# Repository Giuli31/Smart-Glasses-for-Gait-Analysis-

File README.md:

# Smart Glasses for Gait Analysis in Parkinson’s Disease 
## Table of contents
* [General info](#general-info)
* [Technologies](#technologies)
* [How To Use](#how-to-use)

## General info
Parkinson’s disease (PD) is one of the most common neurodegenerative disorders of the central nervous system, which predominantly affects patients’ motor functions, movement, and stability. In recent years, there has been an increase in the usage of wearable sensors for PD symptom monitoring aiming at anticipating the disease diagnosis and thus providing a most efficient quality of care. In this context, the developed device aims to provide objective information on the motor state, analysing the patient's gait and classifying it. In order to accomplish this task, the SGGA device is based on the Timed Up and Go (TUG) test. This is a simple test to measure a person’s level of mobility. It measures the time it takes for a person to get up from a chair, walk three meters, turn around, return to the chair and sit down again. Some sources suggest that a score of 10 seconds or less indicates normal mobility; times between 11 and 20 seconds are within normal limits for elderly with fragility and disabled patients; times longer than 20 seconds indicate that the person needs external assistance and the need for further examinations and interventions. A score greater than 30 seconds suggests that the person may be prone to falls. The TUG was developed from a more articulated test, the Get-up and Go. The SGGA device isn't a classifier of Parkinson’s disease, but it can be a useful tool for the study of symptoms and progression of this disease. 

## Technologies
Project is created with:
* EAGLE - for the design of the PCB
* PSoC Creator - for the program of the microcontroller 
* PyQt5 - for the development the graphical user interface

## How To Use
* [Physical Device](#physical-device)
* [Interface](#interface)
* [Acquisition](#acquisition)
* [Bugs](#bugs)

### Physical Device
The SGGA device is a wearable device composed by two main parts. The first is a small case equipped with accelerometer and wearable on the own glasses or given glasses. The second part is a bigger case that contains the PCB and its components. It's equipped with a belt that must be fastened around the patient’s waist. On the short side of the case, it's possible to check the state of the SGGA device thanks to the presence of two LEDs. The red LED shows that the device is powered, so it works. The green LED shows the connection established between the device and the application. In particular, the green flashing LED indicates that the device is ready to send data to the application, while, when the green LED becomes fixed, it indicates that the device is sending data registered by the accelerometer to the application. 

### Interface
The graphic user interface allows the user to visualize the results of the Timed Up and Go (TUG) test. On the right side of the screen, it is possible to see a graph that shows the acceleration trend over time. On the left side there are two tabs: "Acquisition" and "Excel files". 
The tab "Acquisition" contains buttons "Start Acquisition", "Stop Acquisition", "Save Data", "New Session" and "Search for device". Here it is also possible to visualize a timer and a steps counter. 
The tab "Excel files" shows past acquisitions that are saved on Excel files named with data and progression number of session. Clicking on one of these files, it is possible to visualize on the screen a number between 0 and 2 that indicates the class of the result (0 - Normal Gait, 1 - Require further examinations, 2 - Patient need assistance). This classification is made using a machine learning model, the Decision Trees, that is trained using a set of acquisitions based on TUG test permed by healthy subject trying also to reproduce the gait of impaired people. 

### Acquisition 
The first step of the acquisition is the preparation of the patient. He/She should wear the belt and place the case on the side so that the LED lights are visible. Red LED will light up when the device is connected to the power supply. After that, the patient must wear glasses equipped with the second smaller case. Let sit the patient in the chair and so he/she is ready for the test. 

Now, the user has to run the application using the Python file named "FinalGUI.py" and start the pairing of the device with the application. Once the GUI is open, the user must push the button "Search for device" in order to connect the device, if the connection is successful the green LED will start flashing. At this point, the device is ready for start the acquisition. 

When the patient is ready to perform the test, the user has to push the button "Start Acquisition" and the timer and the steps counter start at the same time. On the graph it's possible to visualize in real-time the acceleration trend of the patient's walk. 

Once the patient has completed the test, the user has to push the button "Stop acquisition". At this point a dynamic window will open and it will show the result of the test, classifying it into "Normal gait detected", "Anomalous gait detected. Further examinations suggested" or "Serious anomalies on gait detected. Subject may require assistances". On the same window, it is asked to the user if he wants to save the result of test, in positive case clicking on "Yes". 

Now it is possible to start a new acquisition pushing again the button "Start Acquisition". 

At the end of the test, it is possible to save the entire session of acquisitions pushing the button "Save Data". These data are saved in files contained in the tab "Excel files". 

In order to start a new session of acquisitions, the user has to push the button "New session" and repeat all the previous steps. 

### Bugs
During the pairing between device and application may happen that the device fails to access the serial port. In this case, a dynamic window will open showing the wrong serial port and the message "ERROR PORT CONNECTION: ". It is recommended to reset the application.

(This project is the result of teamwork)

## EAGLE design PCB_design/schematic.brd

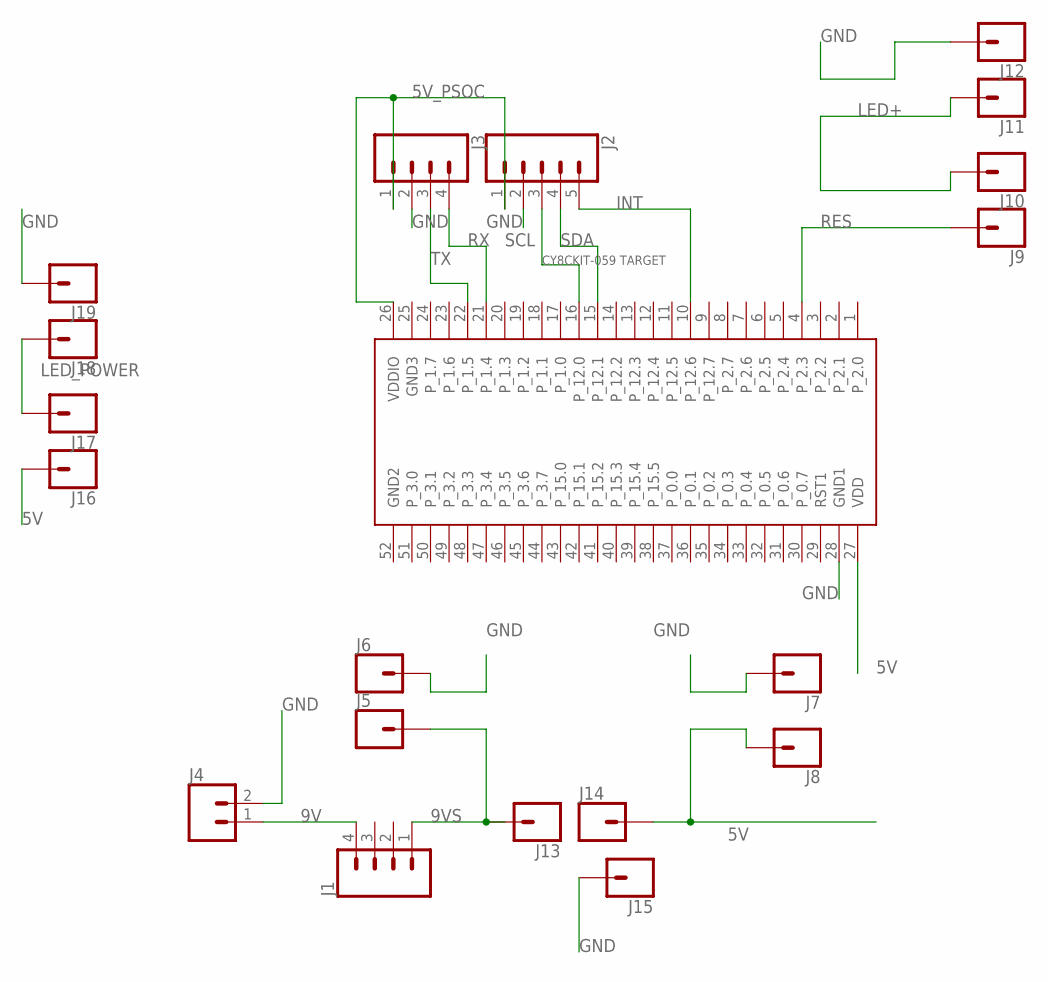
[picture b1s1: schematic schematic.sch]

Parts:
J1, J3: CONN_041X04_NO_SILK; 1X04_NO_SILK
J2: CONN_05NO_SILK; 1X05_NO_SILK
J4: CONN_021X02_NO_SILK; 1X02_NO_SILK
J5, J6, J7, J8, J9, J10, J11, J12, J13, J14, J15, J16, J17, J18, J19: CONN_01PTH_NO_SILK_YES_STOP; 1X01_NO_SILK
U$2: CY8CKIT-059_TARGET_3

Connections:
5V: J8.1, J14.1, J16.1, U$2.27 (VDD)
5V_PSOC: J2.1, J3.1, U$2.26 (VDDIO)
9V: J1.4, J4.1
9VS: J1.1, J5.1, J13.1
GND: J2.2, J3.2, J4.2, J6.1, J7.1, J12.1, J15.1, J19.1, U$2.28 (GND1)
GND2: U$2.52 (GND2)
GND3: U$2.25 (GND3)
INT: J2.5, U$2.10 (P_12.6)
LED+: J10.1, J11.1
LED_POWER: J17.1, J18.1
RES: J9.1, U$2.4 (P_2.3)
RX: J3.4, U$2.21 (P_1.4)
SCL: J2.3, U$2.16 (P_12.0)
SDA: J2.4, U$2.15 (P_12.1)
TX: J3.3, U$2.22 (P_1.5)

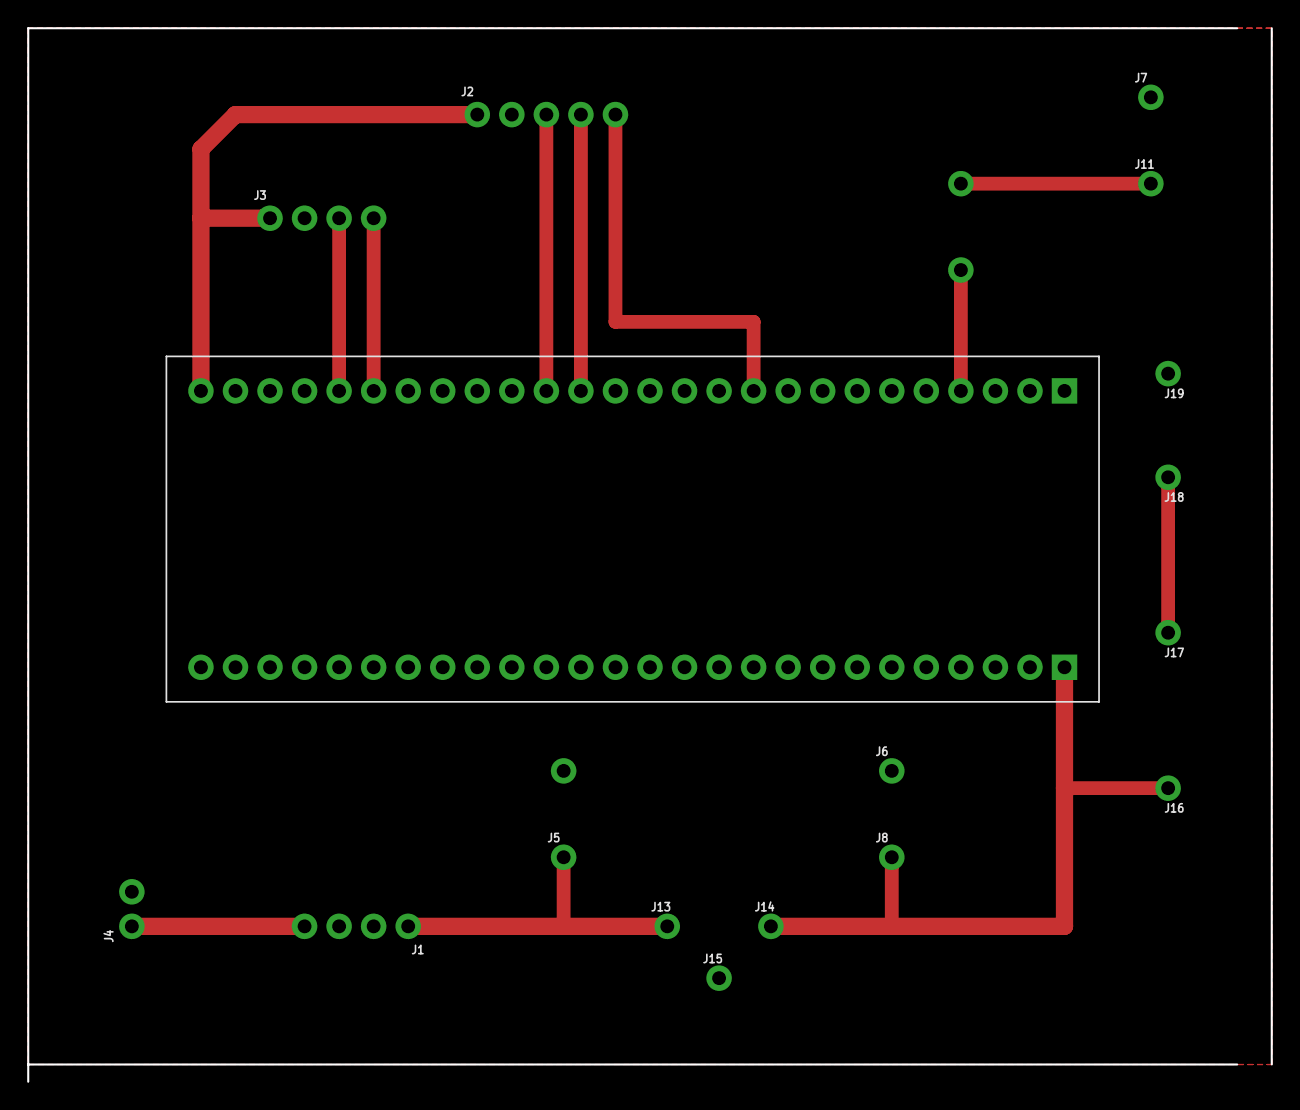
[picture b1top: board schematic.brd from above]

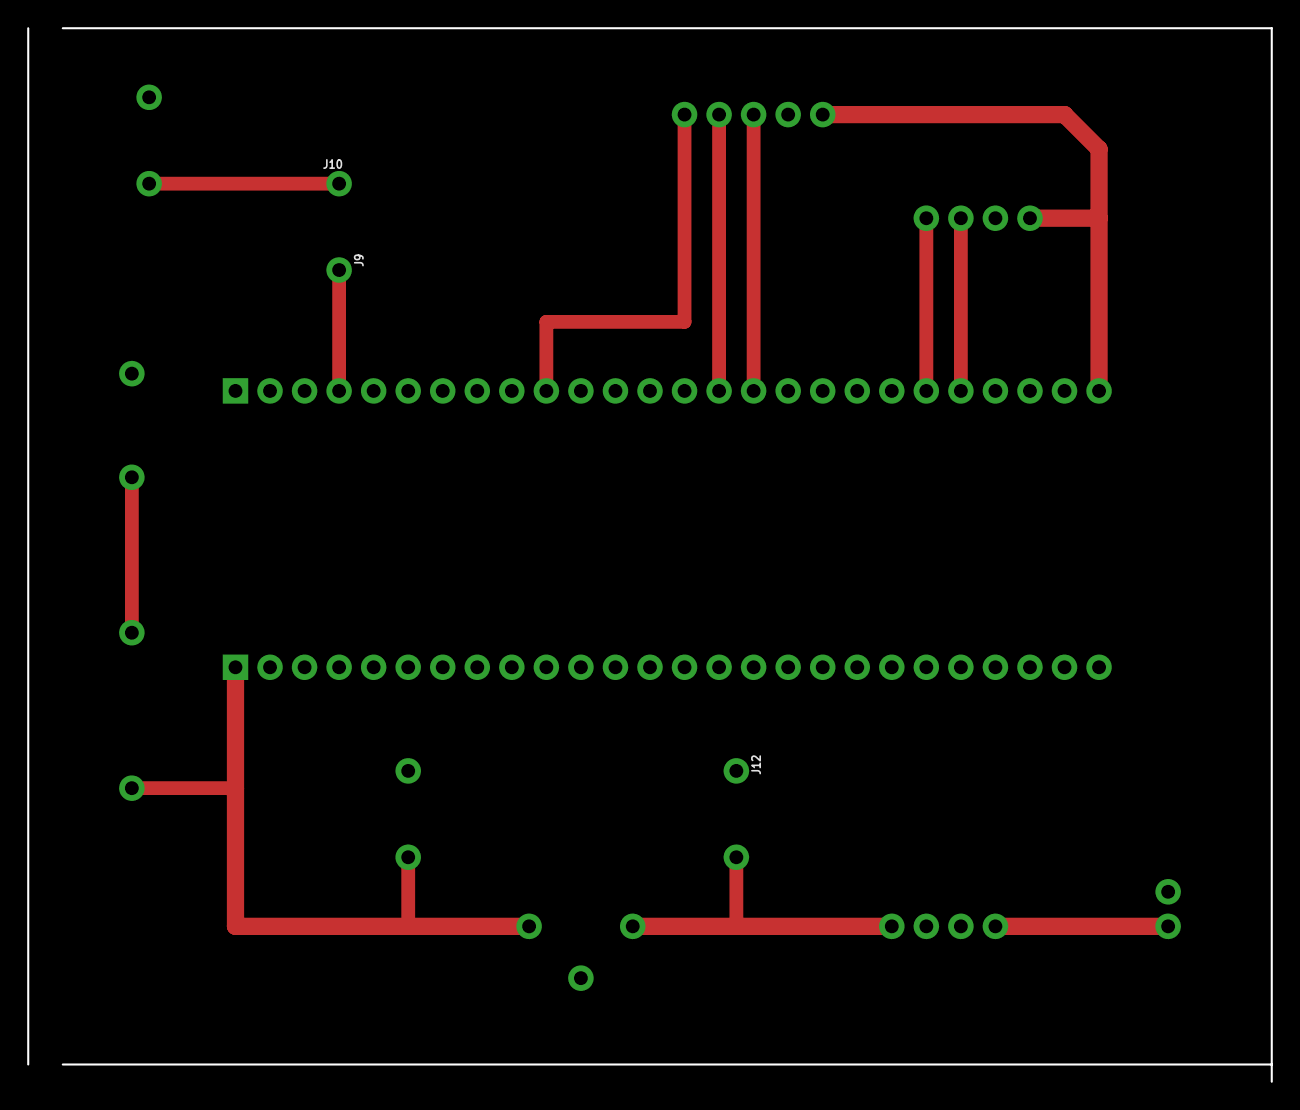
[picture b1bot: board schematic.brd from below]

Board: 2 copper layers, 91.4 x 77.5 mm, 20 parts (3 on the bottom side), 13 nets.

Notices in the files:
parts and their libraries:
SparkFun-Connectors: Licensing: Creative Commons ShareAlike 4.0 International - https://creativecommons.org/licenses/by-sa/4.0
